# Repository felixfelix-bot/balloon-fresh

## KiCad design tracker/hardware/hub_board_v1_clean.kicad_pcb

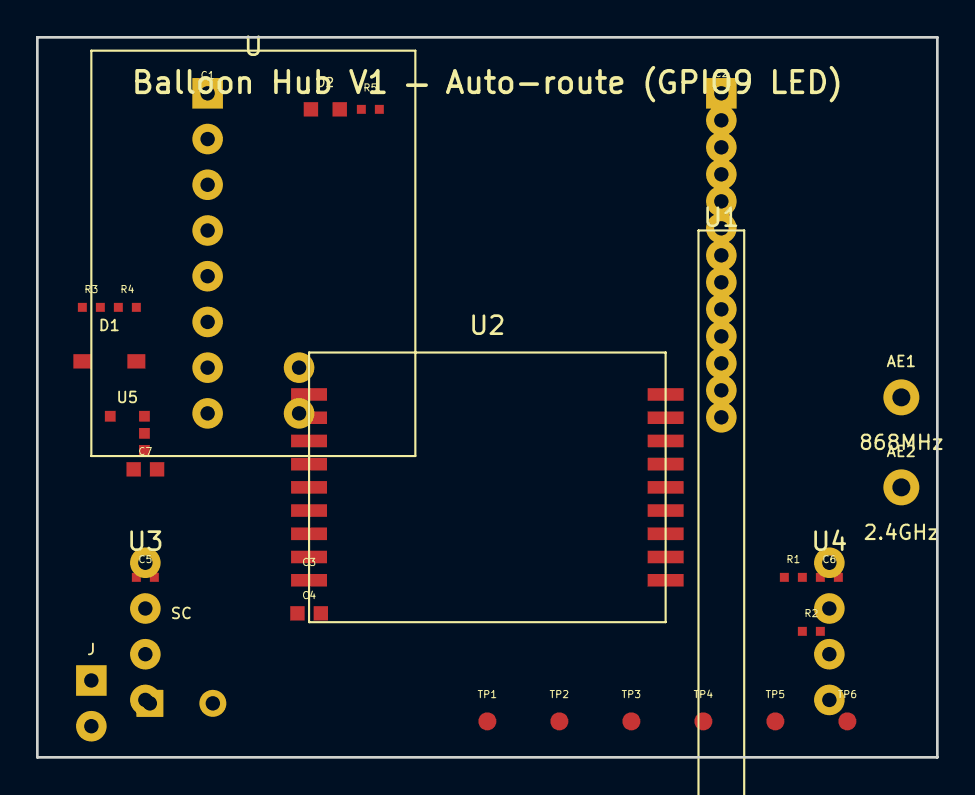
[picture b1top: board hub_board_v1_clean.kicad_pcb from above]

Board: 2 copper layers, 50.0 x 40.0 mm, 30 parts (0 on the bottom side), 21 nets, no tracks yet.

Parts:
AE1: 868MHz; TestPoint_THTPad_D2.0mm_Drill1.0mm
AE2: 2.4GHz; TestPoint_THTPad_D2.0mm_Drill1.0mm
C1, C2, C3, C5, C6: 100nF; C_0402_1005Metric
C4, C7: 10uF; C_0805_2012Metric
D1: BAT54; D_SOD-123
D2: STATUS; LED_0603_1608Metric
J: SOLAR; PinHeader_1x02_P2.54mm_Vertical
R1, R2: 4.7k; R_0402_1005Metric
R3, R4: 1M; R_0402_1005Metric
R5: 330R; R_0402_1005Metric
SC: 1F 5.5V; CP_Radial_D8.0mm_P3.50mm
TP1: SPI0_SCK; TestPoint_Pad_D1.0mm
TP2: SPI0_MOSI; TestPoint_Pad_D1.0mm
TP3: 3V3; TestPoint_Pad_D1.0mm
TP4: GND; TestPoint_Pad_D1.0mm
TP5: LED_GPIO18; TestPoint_Pad_D1.0mm
TP6: FEM_TX_GPIO19; TestPoint_Pad_D1.0mm
U: ESP32-C3-Mini-1; ESP32-C3_Mini_V1_Header
U1: RP2040-Zero; PinHeader_1x13_P2.54mm_Vertical
U2: LoRa2021; LoRa2021_Castellated
U3: MAX-M10S; PinHeader_1x04_P2.54mm_Vertical
U4: MS5611; PinHeader_1x04_P2.54mm_Vertical
U5: TPS7A02; SOT-23-5

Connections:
3V3: C1.1, C2.1, C3.1, C4.1, C5.1, C6.1, C7.1, R1.1, R2.1, TP3.1, U.1, U1.1, U2.1, U3.1, U4.1, U5.5
ESP_TX_RP2040_RX: U.3, U1.12
GND: C1.2, C2.2, C3.2, C4.2, C5.2, C6.2, C7.2, D2.1, J.2, R4.2, SC.2, TP4.1, U.2, U1.2, U1.13, U2.2, U2.8, U2.11, U2.12, U2.18, U3.2, U4.2, U5.2
GPS_TX_ESP_RX: U.5, U3.3
I2C_SCL: R2.2, U.8, U4.4
I2C_SDA: R1.2, U.7, U4.3
LED_ANODE: D2.2, R5.2
LR2021_BUSY: U1.7, U2.7
LR2021_DIO9: U1.8, U2.15
LR2021_RST: U1.9, U2.14
RF_2G4_2400: AE2.1, U2.10
RF_SUB_868: AE1.1, U2.9
RP2040_TX_ESP_RX: U.4, U1.11
SOLAR_IN: D1.1, J.1
SPI0_MISO: U1.5, U2.3
SPI0_MOSI: TP2.1, U1.4, U2.4
SPI0_NSS: U1.6, U2.6
SPI0_SCK: TP1.1, U1.3, U2.5
STATUS_LED: R5.1, TP5.1
VCAP: D1.2, R3.1, SC.1, U5.1, U5.3
VDIV_MID: R3.2, R4.1, U.6

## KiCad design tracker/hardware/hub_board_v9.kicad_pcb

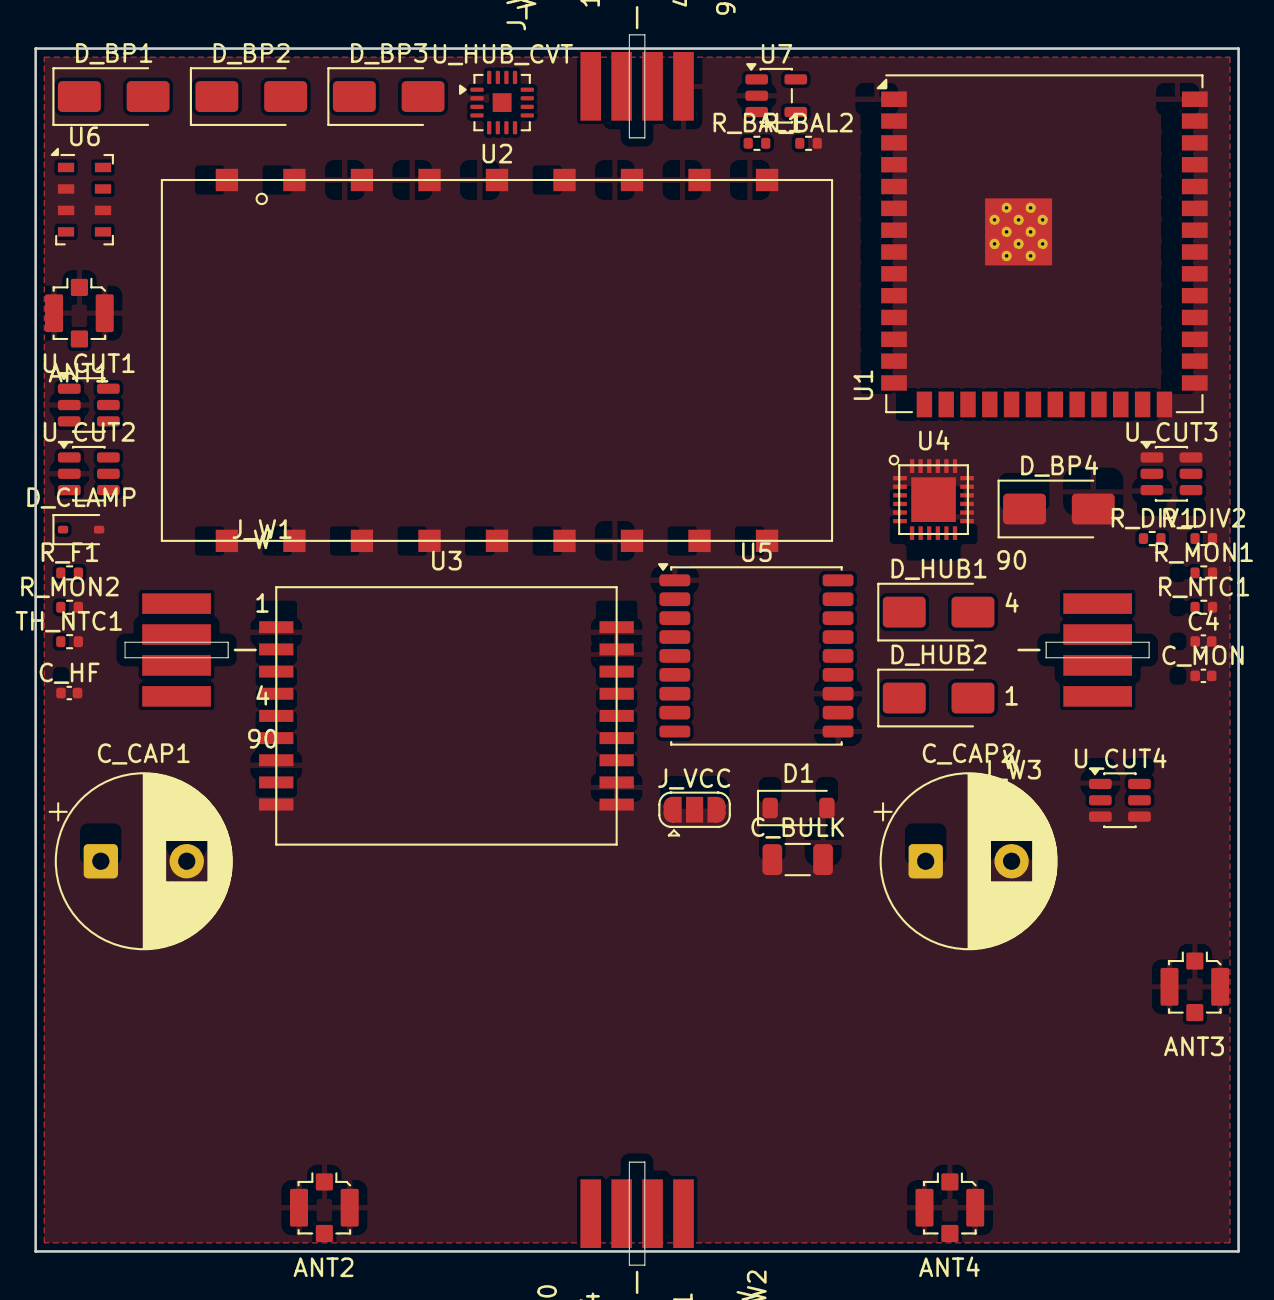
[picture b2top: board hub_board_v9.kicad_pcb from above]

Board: 4 copper layers, 70.0 x 71.6 mm, 44 parts (0 on the bottom side), 51 nets, no tracks yet.

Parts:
ANT1: U.FL_433_TX; U.FL_Molex_MCRF_73412-0110_Vertical
ANT2: U.FL_2G4_RANGE; U.FL_Molex_MCRF_73412-0110_Vertical
ANT3: U.FL_2G4_RX; U.FL_Molex_MCRF_73412-0110_Vertical
ANT4: U.FL_GNSS_L1; U.FL_Molex_MCRF_73412-0110_Vertical
C4: 10uF; C_0402_1005Metric
C_BULK: 100uF; C_1206_3216Metric
C_CAP1, C_CAP2: 3.3F 2.7V (AVX SCC); CP_Radial_D10.0mm_P5.00mm
C_HF: 100nF; C_0402_1005Metric
C_MON: 10nF; C_0402_1005Metric
D1: BAT54; D_SOD-123
D_BP1, D_BP2, D_BP3, D_BP4: SS24; D_SMA
D_CLAMP: TVS clamp (set point TODO(unverified)); D_SOD-323
D_HUB1, D_HUB2: SS24; D_SMA
J_VCC: F33_VCC_SEL (5V raw | 3V3); SolderJumper-3_P1.3mm_Open_RoundedPad1.0x1.5mm
J_W1: WING_SOCKET_4P (hub wing interface 1); Wing_Tab_4P
J_W2: WING_SOCKET_4P (hub wing interface 2); Wing_Tab_4P
J_W3: WING_SOCKET_4P (hub wing interface 3); Wing_Tab_4P
J_W4: WING_SOCKET_4P (hub wing interface 4); Wing_Tab_4P
R_BAL1, R_BAL2: 10k; R_0402_1005Metric
R_DIV1, R_DIV2: 1M; R_0402_1005Metric
R_F1: 100R; R_0402_1005Metric
R_MON1, R_MON2: 4.7M; R_0402_1005Metric
R_NTC1: TODO(unverified) (sets ntc_r_ratio); R_0402_1005Metric
TH_NTC1: TODO(unverified) (NTC, R25/beta TODO); R_0402_1005Metric
U1: ESP32-S3-WROOM-1U-N8R8; ESP32-S3-WROOM-1U
U2: LoRa2021F33-2G4; LoRa2021F33_2G4
U3: LoRa2021_Castellated
U4: SX1280; SX1280_QFN24
U5: MAX-M10S; ublox_MAX
U6: MS5611-01BA; LGA-8_3x5mm_P1.25mm
U7: TPS7A02; SOT-23-5
U_CUT1, U_CUT2, U_CUT3, U_CUT4: SN74LVC1G373DBVR; SOT-23-6
U_HUB_CVT: BQ25504RGTR; VQFN-16-1EP_3x3mm_P0.5mm_EP1.1x1.1mm

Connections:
+3V3: J_VCC.3, R_F1.1, U1.2, U2.5, U3.1, U4.1, U4.2, U5.6, U5.7, U5.9, U6.1, U6.4, U6.5, U7.5
/ANT1_433_TX: ANT1.1, U2.9
/ANT2_2G4_RANGE: ANT2.1, U4.14
/ANT3_2G4_RX: ANT3.1, U3.10
/ANT4_GNSS_L1: ANT4.1, U5.11
/CUT_SENSE_W1: J_W1.3, U_CUT1.3
/CUT_SENSE_W2: J_W2.3, U_CUT2.3
/CUT_SENSE_W3: J_W3.3, U_CUT3.3
/CUT_SENSE_W4: J_W4.3, U_CUT4.3
/F33_BUSY: U1.12, U2.14
/F33_CS_N: U1.7, U2.13
/F33_IRQ: U1.17, U2.18
/F33_MISO: U1.6, U2.16, U3.3
/F33_MOSI: U1.5, U2.15, U3.4
/F33_RESET_N: U1.18, U2.17
/F33_SCK: U1.4, U2.12, U3.5
/F33_VCC: C_BULK.1, C_HF.1, D_CLAMP.1, J_VCC.2, R_MON1.1, U2.1
/F33_VSENSE: C_MON.1, R_MON1.2, R_MON2.1, U1.21
/GNSS_PPS: U1.23, U5.4
/GNSS_RX: U1.37, U5.3
/GNSS_TX: U1.36, U5.2
/GNSS_VCC: C4.1, R_F1.2, U5.8
/HUB_PV_MID1: D_HUB1.2, D_HUB2.1
/HUB_PV_N: D_HUB2.2, U_HUB_CVT.3
/HUB_PV_P: D_HUB1.1, U_HUB_CVT.1
/I2C_SCL: U1.38, U6.8
/I2C_SDA: U1.39, U6.7
/NTC_SENSE: R_NTC1.2, TH_NTC1.1
/SCAP_ADC: R_DIV1.2, R_DIV2.1
/SCAP_MID: C_CAP1.2, C_CAP2.1, R_BAL1.2, R_BAL2.1
/SX1280_ANT_SW: U1.35, U4.13
/SX1280_BUSY: U1.31, U4.5
/SX1280_CS_N: U1.10, U4.6
/SX1280_DIO1: U1.33, U4.10
/SX1280_DIO2: U1.11, U4.11
/SX1280_DIO3: U1.34, U4.12
/SX1280_MISO: U1.9, U4.9
/SX1280_MOSI: U1.8, U4.8
/SX1280_RESET_N: U1.32, U4.4
/SX1280_SCK: U1.22, U4.7
/U3_BUSY: U1.24, U3.7
/U3_CS_N: U1.20, U3.6
/U3_IRQ: U1.19, U3.15
/U3_RESET_N: U1.25, U3.14
/VSCAP: C_CAP1.1, D1.1, J_VCC.1, R_BAL1.1, R_DIV1.1, U7.1, U7.3, U_CUT1.1, U_CUT2.1, U_CUT3.1, U_CUT4.1
/VTCXO_VNTC: R_NTC1.1, U3.13
/W1_SOLAR_N: D_BP1.2, D_BP2.1, J_W1.4, J_W2.1
/W1_SOLAR_P: D1.2, D_BP1.1, J_W1.1
/W2_SOLAR_N: D_BP2.2, D_BP3.1, J_W2.4, J_W3.1
/W3_SOLAR_N: D_BP3.2, D_BP4.1, J_W3.4, J_W4.1
GND: ANT1.2, ANT2.2, ANT3.2, ANT4.2, C4.2, C_BULK.2, C_CAP2.2, C_HF.2, C_MON.2, D_BP4.2, D_CLAMP.2, J_W1.2, J_W2.2, J_W3.2, J_W4.2, J_W4.4, R_BAL2.2, R_DIV2.2, R_MON2.2, TH_NTC1.2, U1.1, U1.40, U1.41, U2.2, U2.3, U2.4, U2.6, U2.7, U2.8, U2.11, U3.2, U3.8, U3.11, U3.12, U3.18, U4.3, U4.15, U4.16, U4.17, U4.18, U4.19, U4.20, U4.21, U4.22, U4.23, U4.24, U4.25, U5.1, U5.10, U5.12, U6.2, U6.3, U6.6, U7.2, U_CUT1.2, U_CUT2.2, U_CUT3.2, U_CUT4.2, U_HUB_CVT.2
